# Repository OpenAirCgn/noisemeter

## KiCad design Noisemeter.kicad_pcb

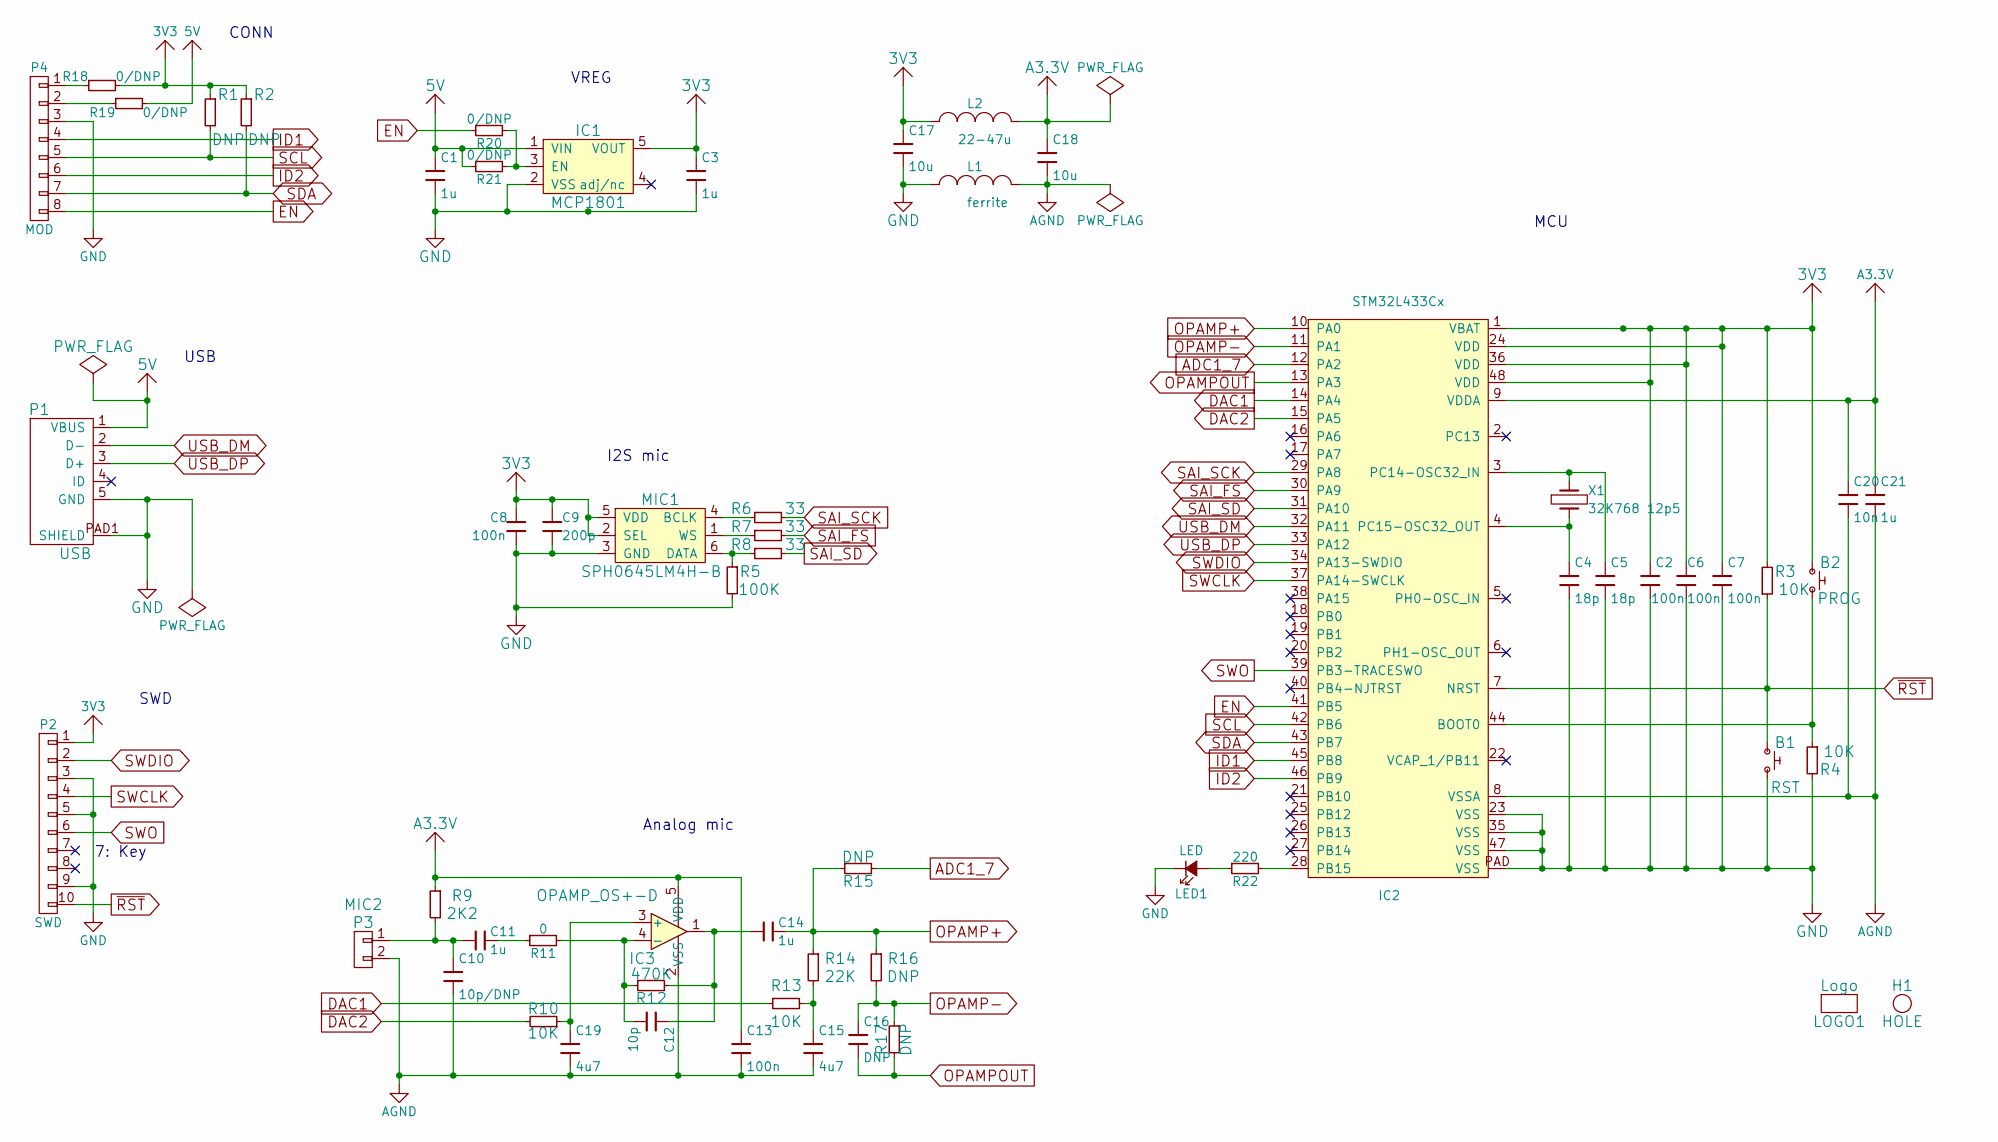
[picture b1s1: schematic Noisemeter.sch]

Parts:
B1: RST; CK-PTS830
B2: PROG; CK-PTS830
C1, C3, C11, C14, C21: 1u; 0603
C2, C6, C7, C8, C13: 100n; 0603
C4, C5: 18p; 0603
C9: 200p; 0603
C10: 10p/DNP; 0603
C12: 10p; 0603
C15, C19: 4u7; 0603
C16: DNP; 0603
C17, C18: 10u; 0603
C20: 10n; 0603
H1: HOLE; HOLE-3.2
IC1: MCP1801; SOT23-5
IC2: STM32L433Cx
IC3: OPAMP_OS+-D; SOT23-5
L1: ferrite; 0603
L2: 22-47u; 0603
LED1: LED; 0603-POLAR
LOGO1: Logo
MIC1: SPH0645LM4H-B; SPH0645LM4H-B-ext
P1: USB; USB-MICRO-B
P2: SWD; HEADER-2x05-1.27
P3: MIC2; HEADER-1x02-2.54
P4: MOD; HEADER-1x08-1.27-ZZ-POL
R1, R2, R15, R16, R17: DNP; 0603
R3, R4, R10, R13: 10K; 0603
R5: 100K; 0603
R6, R7, R8: 33; 0603
R9: 2K2; 0603
R11: 0; 0603
R12: 470K; 0603
R14: 22K; 0603
R18, R19, R20, R21: 0/DNP; 0603
R22: 220; 0603
X1: 32K768 12p5; 1206

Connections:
3V3: B2.1, C2.1, C3.1, C6.1, C7.1, C8.1, C9.1, C17.1, IC1.5 (VOUT), IC2.1 (VBAT), IC2.24 (VDD), IC2.36 (VDD), IC2.48 (VDD), L2.1, MIC1.2 (SEL), MIC1.5 (VDD), P2.1, R1.1, R2.1, R3.2, R18.2
ADC1_7: IC2.12 (PA2), R15.2
DAC1: IC2.14 (PA4), R13.1
DAC2: IC2.15 (PA5), R10.2
EN: IC2.41 (PB5), P4.8, R20.1
ID1: IC2.45 (PB8), P4.4
ID2: IC2.46 (PB9), P4.6
unnamed: B2.2, IC2.44 (BOOT0), R4.1
unnamed: C4.1, IC2.4 (PC15-OSC32_OUT), X1.2
unnamed: C5.1, IC2.3 (PC14-OSC32_IN), X1.1
unnamed: C10.1, C11.2, P3.1, R9.2
unnamed: C11.1, R11.1
unnamed: C12.1, C14.2, IC3.1, R12.2
unnamed: C12.2, IC3.4 (-), R11.2, R12.1
unnamed: C15.1, R13.2, R14.2
unnamed: C19.1, IC3.3 (+), R10.1
unnamed: IC1.3 (EN), R20.2, R21.2
unnamed: IC2.28 (PB15), R22.2
unnamed: LED1.A, R22.1
unnamed: MIC1.1 (WS), R7.1
unnamed: MIC1.4 (BCLK), R6.1
unnamed: MIC1.6 (DATA), R5.1, R8.1
unnamed: P4.1, R18.1
unnamed: P4.2, R19.1
OPAMP+: C14.1, IC2.10 (PA0), R14.1, R15.1, R16.1
OPAMP-: C16.1, IC2.11 (PA1), R16.2, R17.1
OPAMPOUT: C16.2, IC2.13 (PA3), R17.2
SAI_FS: IC2.30 (PA9), R7.2
SAI_SCK: IC2.29 (PA8), R6.2
SAI_SD: IC2.31 (PA10), R8.2
SCL: IC2.42 (PB6), P4.5, R1.2
SDA: IC2.43 (PB7), P4.7, R2.2
SWCLK: IC2.37 (PA14-SWCLK), P2.4
SWDIO: IC2.34 (PA13-SWDIO), P2.2
SWO: IC2.39 (PB3-TRACESWO), P2.6
USB_DM: IC2.32 (PA11), P1.2 (D-)
USB_DP: IC2.33 (PA12), P1.3 (D+)
~RST: B1.1, IC2.7 (NRST), P2.10, R3.1

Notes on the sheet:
I2S mic
VREG
USB
CONN
Analog mic
7: Key
SWD
MCU

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
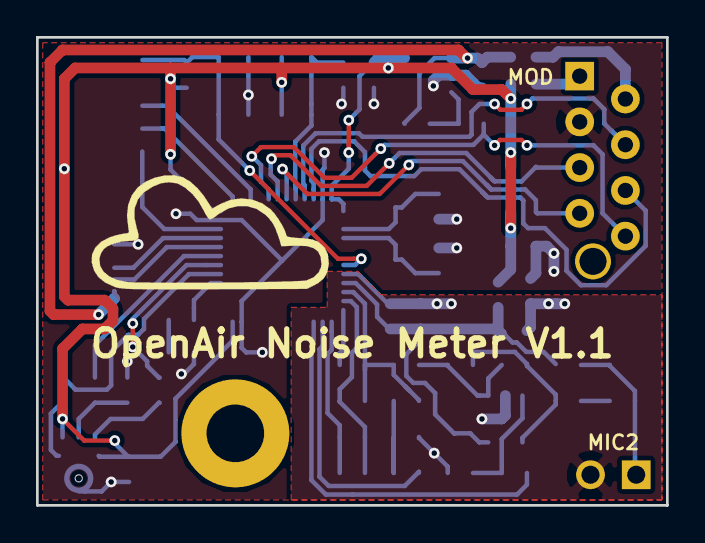
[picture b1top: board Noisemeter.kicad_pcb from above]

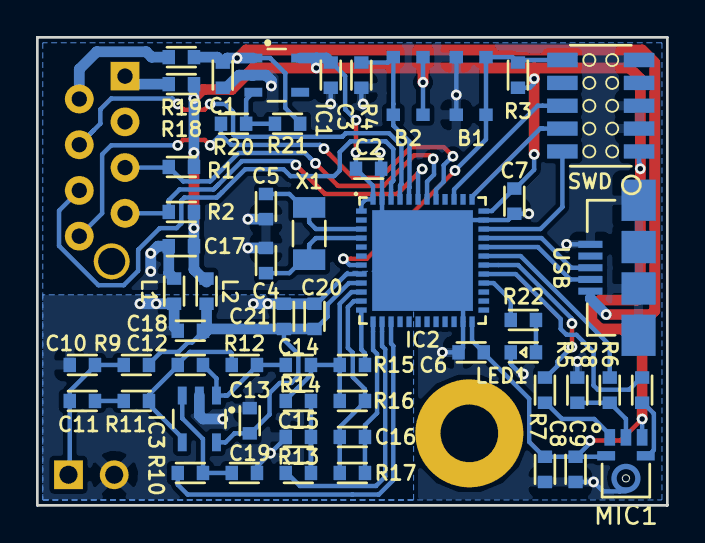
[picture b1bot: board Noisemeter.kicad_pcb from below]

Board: 2 copper layers, 35.0 x 26.0 mm, 59 parts (55 on the bottom side), 42 nets.

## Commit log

2019-01-24 Initial version
2019-06-06 Added BOM
2019-06-13 Version 1.0
2019-06-14 Fixed analog power supply
2019-08-29 minor changes, BOM rename
2020-03-10 README
